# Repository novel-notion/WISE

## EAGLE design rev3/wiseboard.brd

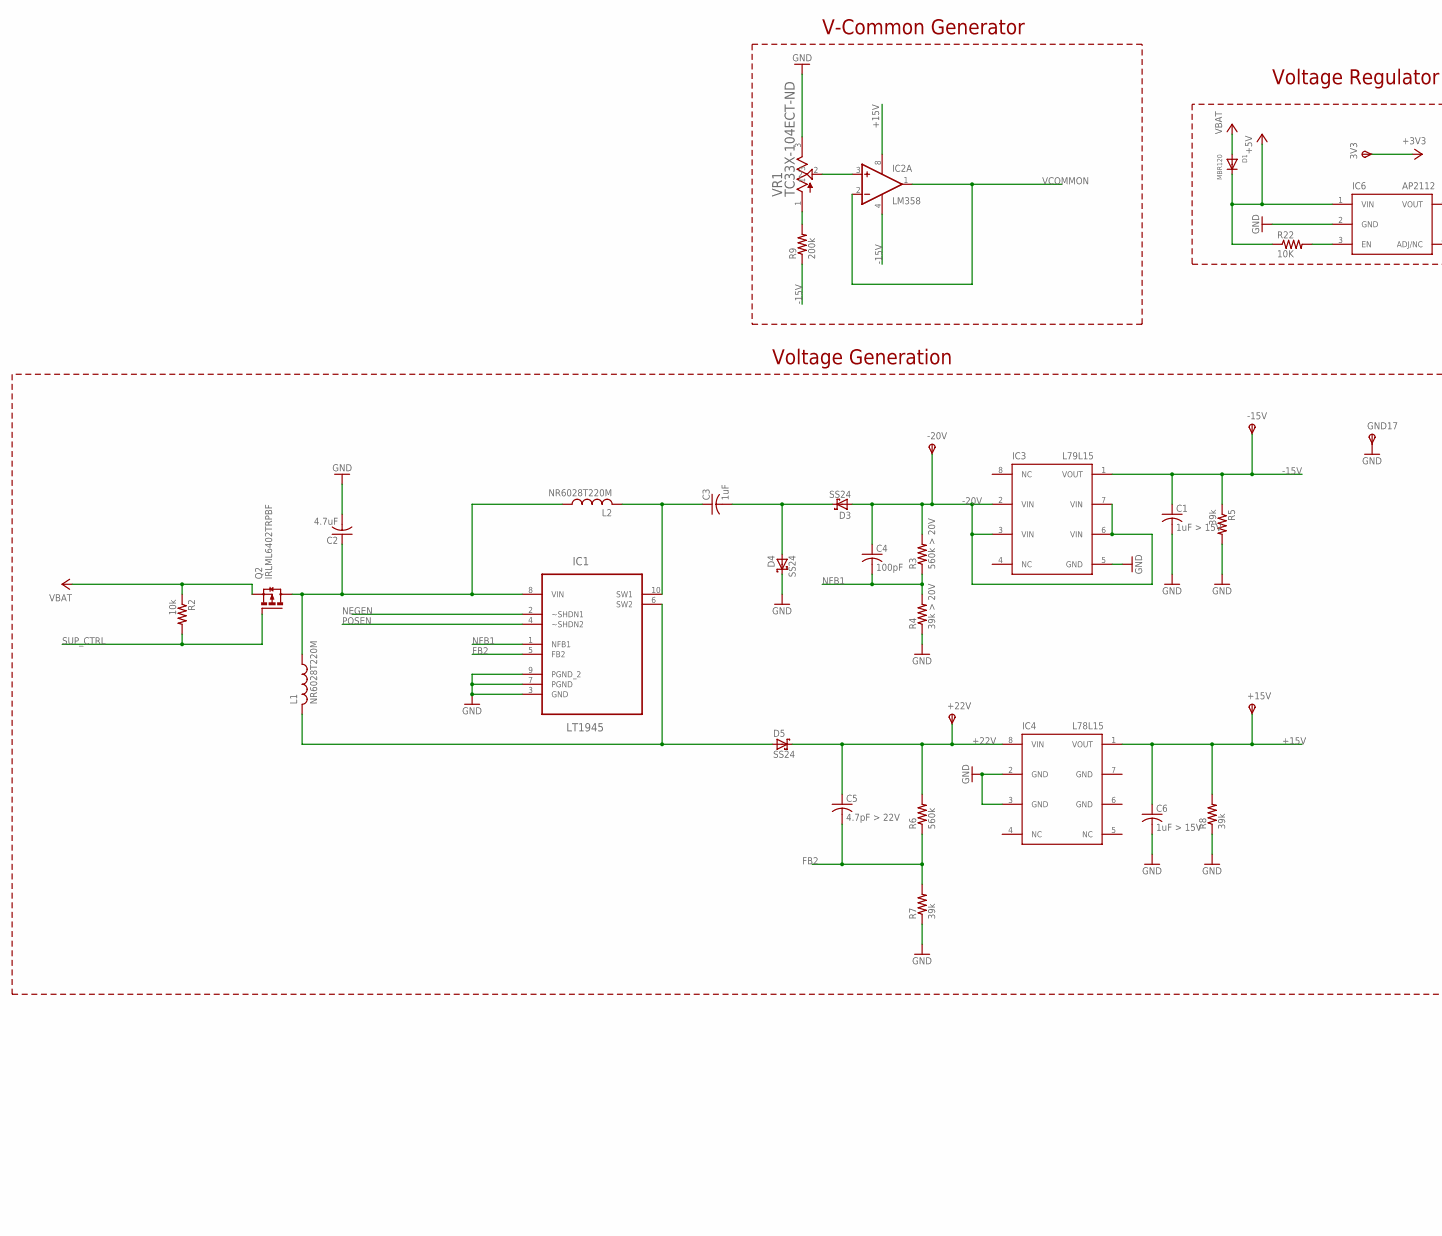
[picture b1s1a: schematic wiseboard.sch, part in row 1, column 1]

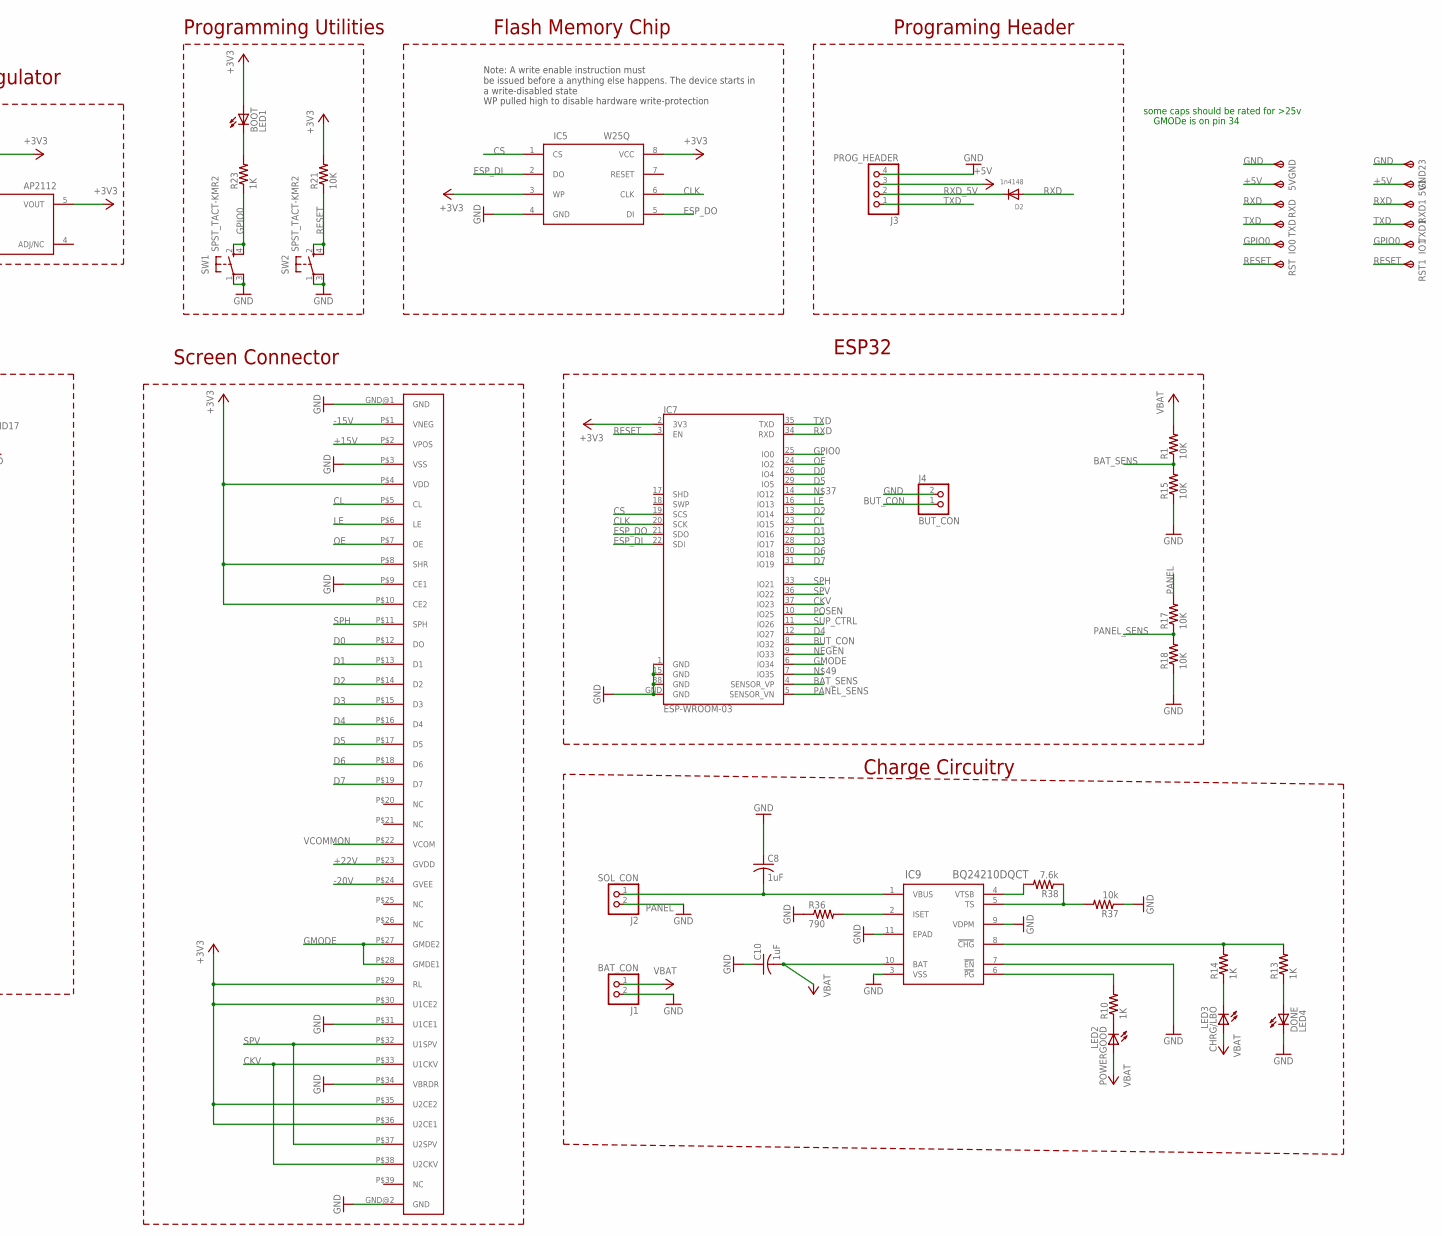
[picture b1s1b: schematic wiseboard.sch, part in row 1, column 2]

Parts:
3V3, 5V, 5V1: TPSTP20R; TP20R
+15V, +22V: TPSTP20R; TP20R
-15V, -20V: TPSTP20R; TP20R
BOOT: LED1; CHIP-LED0805
C1, C6: 1uF > 15V; C0805
C2: 4.7uF; C0805
C3, C8, C10: 1uF; C0805
C4: 100pF; C0805
C5: 4.7pF > 22V; C0805
CHRG/LBO: LED3; CHIP-LED0805
D1: MBR120; SOD-123
D2: 1n4148; SOD-123
D3, D4, D5: SS24; DO214AA
DONE: LED4; CHIP-LED0805
GND, GND17, GND23: TPSTP20SQ; TP20SQ
IC1: LT1945; SOP50P490X110-10N
IC2: LM358; SO08
IC3: L79L15; SO8
IC4: L78L15; SO8
IC5: W25Q; SO8
IC6: AP2112; SOT95P280X145-5N
IC7: ESP-WROOM-03
IC9: BQ24210DQCT; DQC10_P84X2P4
IO0, IO1: TPSTP20R; TP20R
J1: BAT_CON; EDGE_CON_2
J2: SOL_CON; EDGE_CON_2
J3: PROG_HEADER; EDGE_CON_4
J4: BUT_CON; EDGE_CON_2
L1, L2: NR6028T220M
POWERGOOD: LED2; CHIP-LED0805
Q2: IRLML6402TRPBF; SOT23
R1, R15, R17, R18, R21, R22: 10K; R0805
R2, R37: 10k; R0805
R3: 560k > 20V; R0805
R4: 39k > 20V; R0805
R5, R7, R8: 39k; R0805
R6: 560k; R0805
R9: 200k; R0805
R10, R13, R14, R23: 1K; R0805
R36: 790; R0805
R38: 7.6k; R0805
RST, RST1: TPSTP20R; TP20R
RXD, RXD1: TPSTP20R; TP20R
SW1, SW2: SPST_TACT-KMR2; KMR2
TXD, TXD1: TPSTP20R; TP20R
U$4: FH26W-39S; HFQ339CT-ND
VR1: TC33X-104ECT-ND; TRIM_TC33X-2-103E

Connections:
+3V3: 3V3.TP, BOOT.A, IC5.3 (WP), IC5.8 (VCC), IC6.5 (VOUT), IC7.2 (3V3), R21.2, U$4.P$4 (VDD), U$4.P$8 (SHR), U$4.P$10 (CE2), U$4.P$29 (RL), U$4.P$30 (U1CE2), U$4.P$35 (U2CE2), U$4.P$36 (U2CE1)
+5V: 5V.TP, 5V1.TP, D1.C, IC6.1 (VIN), J3.3, R22.1
+15V: +15V.TP, C6.1, IC2.8 (V+), IC4.1 (VOUT), R8.2, U$4.P$2 (VPOS)
+22V: +22V.TP, C5.1, D5.C, IC4.8 (VIN), R6.2, U$4.P$23 (GVDD)
-15V: -15V.TP, C1.1, IC2.4 (V-), IC3.1 (VOUT), R5.1, R9.1, U$4.P$1 (VNEG)
-20V: -20V.TP, C4.1, D3.A, IC3.2 (VIN), IC3.3 (VIN), IC3.6 (VIN), IC3.7 (VIN), R3.2, U$4.P$24 (GVEE)
BAT_SENS: IC7.4 (SENSOR_VP), R1.1, R15.2
BUT_CON: IC7.8 (IO32), J4.1 (2)
CKV: IC7.37 (IO23), U$4.P$33 (U1CKV), U$4.P$38 (U2CKV)
CL: IC7.23 (IO15), U$4.P$5 (CL)
CLK: IC5.6 (CLK), IC7.20 (SCK)
CS: IC5.1 (CS), IC7.19 (SCS)
D0: IC7.26 (IO4), U$4.P$12 (DO)
D1: IC7.27 (IO16), U$4.P$13 (D1)
D2: IC7.13 (IO14), U$4.P$14 (D2)
D3: IC7.28 (IO17), U$4.P$15 (D3)
D4: IC7.12 (IO27), U$4.P$16 (D4)
D5: IC7.29 (IO5), U$4.P$17 (D5)
D6: IC7.30 (IO18), U$4.P$18 (D6)
D7: IC7.31 (IO19), U$4.P$19 (D7)
ESP_DI: IC5.2 (DO), IC7.22 (SDI)
ESP_DO: IC5.5 (DI), IC7.21 (SDO)
FB2: C5.2, IC1.5 (FB2), R6.1, R7.2
GMODE: IC7.6 (IO34), U$4.P$27 (GMDE2), U$4.P$28 (GMDE1)
GND: C1.2, C2.2, C6.2, C8.1, C10.1, D4.C, DONE.C, GND.TP, GND17.TP, GND23.TP, IC1.3 (GND), IC1.7 (PGND), IC1.9 (PGND_2), IC3.5 (GND), IC4.2 (GND), IC4.3 (GND), IC5.4 (GND), IC6.2 (GND), IC7.1 (GND), IC7.15 (GND), IC7.38 (GND), IC7.GND, IC9.3 (VSS), IC9.7 (!EN), IC9.9 (VDPM), IC9.11 (EPAD), J1.2 (1), J2.2 (1), J3.4, J4.2 (1), R4.1, R5.2, R7.1, R8.1, R15.1, R18.1, R36.1, R37.1, SW1.1, SW1.3 (P1), SW2.1, SW2.3 (P1), U$4.GND@1 (GND), U$4.GND@2 (GND), U$4.P$3 (VSS), U$4.P$9 (CE1), U$4.P$31 (U1CE1), U$4.P$34 (VBRDR), VR1.3
GPIO0: IC7.25 (IO0), IO0.TP, IO1.TP, R23.1, SW1.2 (S), SW1.4 (S1)
LE: IC7.16 (IO13), U$4.P$6 (LE)
unnamed: IC2.3 (+IN), VR1.2
unnamed: C3.1, IC1.10 (SW1), L2.P$2 (2)
unnamed: C2.1, IC1.8 (VIN), L1.P$1 (1), L2.P$1 (1), Q2.3 (D)
unnamed: D5.A, IC1.6 (SW2), L1.P$2 (2)
unnamed: C3.2, D3.C, D4.A
unnamed: R9.2, VR1.1
unnamed: IC9.6 (!PG), R10.2
unnamed: CHRG/LBO.C, R14.1
unnamed: POWERGOOD.C, R10.1
unnamed: DONE.A, R13.1
unnamed: IC9.8 (!CHG), R13.2, R14.2
unnamed: IC9.2 (ISET), R36.2
unnamed: BOOT.C, R23.2
unnamed: IC6.3 (EN), R22.2
unnamed: IC9.5 (TS), R37.2, R38.1
unnamed: IC9.4 (VTSB), R38.2
NEGEN: IC1.2 (~SHDN1), IC7.9 (IO33)
NFB1: C4.2, IC1.1 (NFB1), R3.1, R4.2
OE: IC7.24 (IO2), U$4.P$7 (OE)
PANEL: C8.2, IC9.1 (VBUS), J2.1 (2), R17.2
PANEL_SENS: IC7.5 (SENSOR_VN), R17.1, R18.2
POSEN: IC1.4 (~SHDN2), IC7.10 (IO25)
RESET: IC7.3 (EN), R21.1, RST.TP, RST1.TP, SW2.2 (S), SW2.4 (S1)
RXD: D2.A, IC7.34 (RXD), RXD.TP, RXD1.TP
RXD_5V: D2.C, J3.2
SPH: IC7.33 (IO21), U$4.P$11 (SPH)
SPV: IC7.36 (IO22), U$4.P$32 (U1SPV), U$4.P$37 (U2SPV)
SUP_CTRL: IC7.11 (IO26), Q2.1 (G), R2.2
TXD: IC7.35 (TXD), J3.1, TXD.TP, TXD1.TP
VBAT: C10.2, CHRG/LBO.A, D1.A, IC9.10 (BAT), J1.1 (2), POWERGOOD.A, Q2.2 (S), R1.2, R2.1
VCOMMON: IC2.1 (OUT), IC2.2 (-IN), U$4.P$22 (VCOM)

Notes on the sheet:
V-Common Generator
Programming Utilities
Programing Header
Voltage Generation
Charge Circuitry
ESP32
Voltage Regulator
Screen Connector
Note: A write enable instruction must be issued before a anything else happens. The device starts in a write-disabled state
WP pulled high to disable hardware write-protection
Flash Memory Chip
some caps should be rated for >25v
GMODe is on pin 34

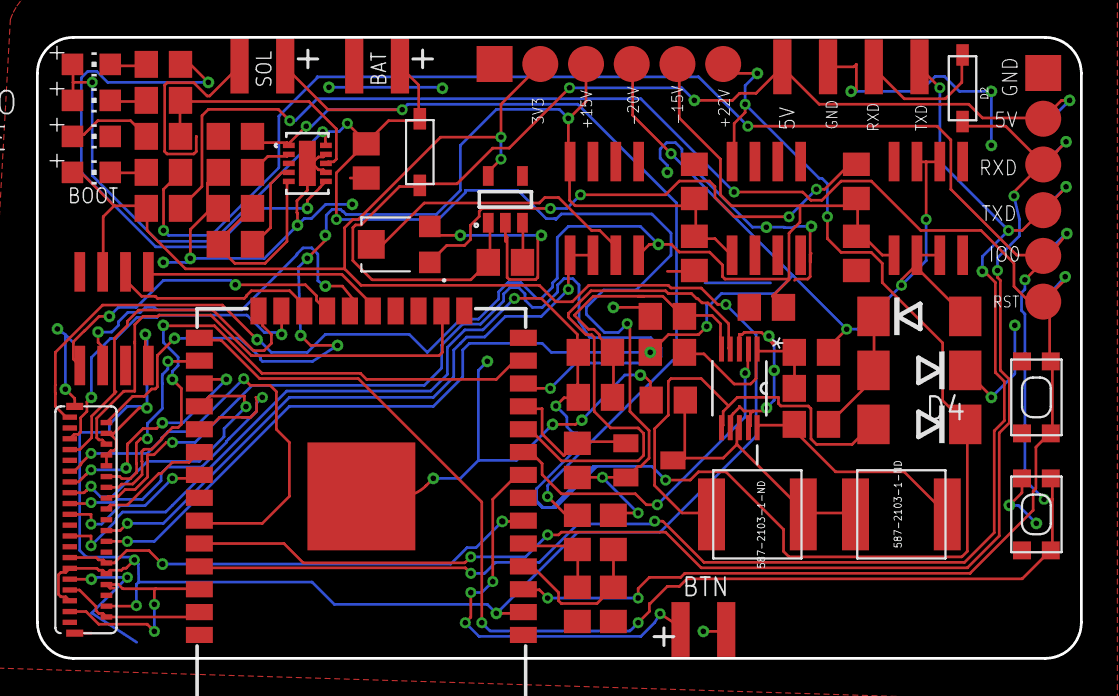
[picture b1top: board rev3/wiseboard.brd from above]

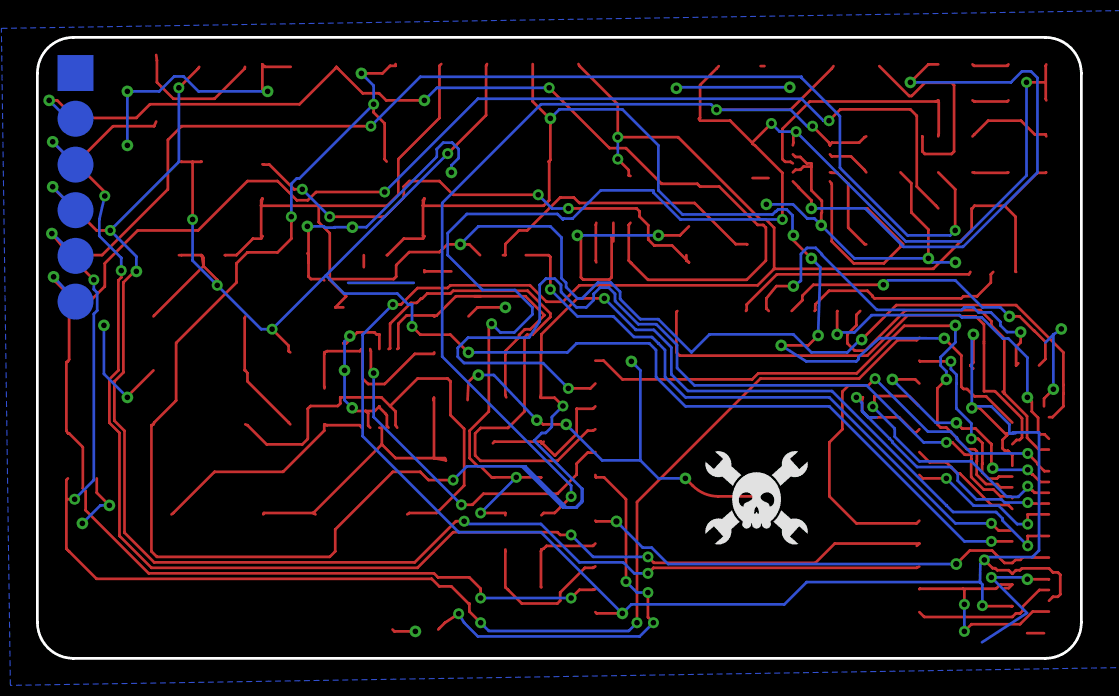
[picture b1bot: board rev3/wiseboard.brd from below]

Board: 2 copper layers, 58.0 x 34.5 mm, 75 parts (6 on the bottom side), 58 nets.

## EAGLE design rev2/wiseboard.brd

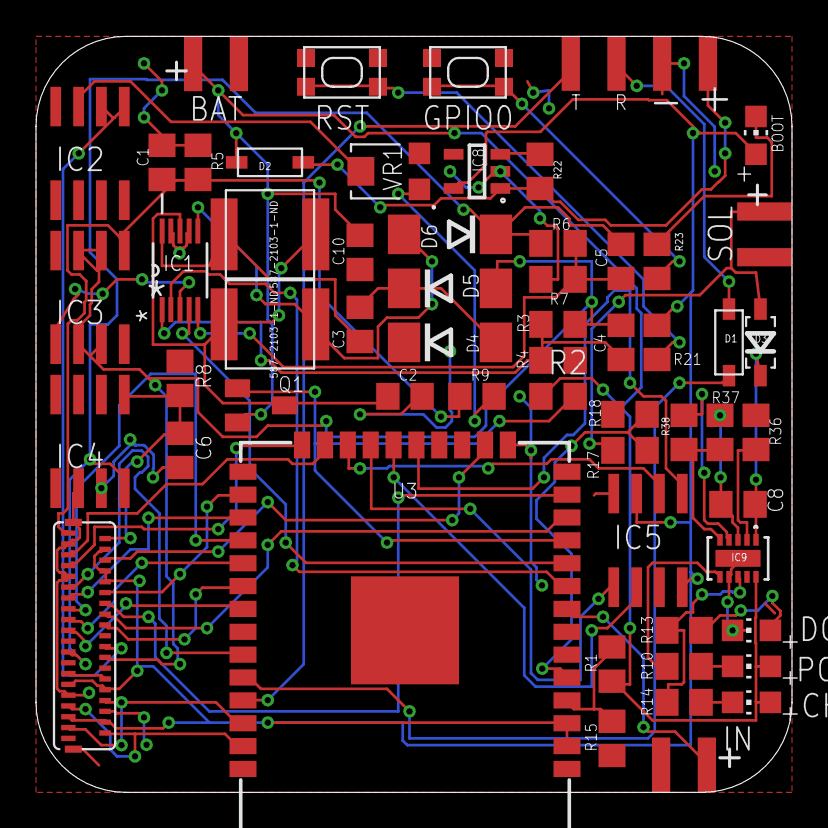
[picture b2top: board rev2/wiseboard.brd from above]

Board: 2 copper layers, 42.0 x 42.0 mm, 58 parts (0 on the bottom side), 59 nets.

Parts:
22: 587-2103-1-ND
BOOT: LED1; CHIP-LED0805
C1, C2, C3, C6: 1uF; C0805
C4, C5, C8, C10: 10uF; C0805
CHRG/LBO: LED3; CHIP-LED0805
D1: MBR120VLSFT1G; SOD-123
D2: MBR120; SOD-123
D3: 1n4148; SOD-123
D4, D5, D6: SS24; DO214AA
DONE: LED4; CHIP-LED0805
IC1: LT1945; SOP50P490X110-10N
IC2: LM358; SO08
IC3: L79L15; SO8
IC4: L78L15; SO8
IC5: W25Q; SO8
IC8: IC6; SOT95P280X145-5N
IC9: BQ24210DQCT; DQC10_P84X2P4
J1: BAT_CON; EDGE_CON_2
J2: SOL_CON; EDGE_CON_2
J3: PROG_HEADER; EDGE_CON_4
J4: BUT_CON; EDGE_CON_2
POWERGOOD: LED2; CHIP-LED0805
Q1: IRLM; SOT23
R1, R15, R17, R18, R21, R22: 10K; R0805
R2, R37: 10k; R0805
R3: 470k; R0805
R4, R5, R7, R8: 39k; R0805
R6: 560k; R0805
R9: 200k; R0805
R10, R13, R14, R23: 1K; R0805
R36: 790; R0805
R38: 7.6k; R0805
SW1, SW2: SPST_TACT-KMR2; KMR2
U3: ESP-WROOM-03
U$4: FH26W-39S; HFQ339CT-ND
U$5: 587-2103-1-ND
VR1: TC33X-104ECT-ND; TRIM_TC33X-2-103E

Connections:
+3V3: BOOT.A, IC5.3, IC5.8, IC8.5, R21.2, U3.2, U3.3, U$4.P$4, U$4.P$8, U$4.P$10, U$4.P$29, U$4.P$30, U$4.P$35, U$4.P$36
+5V: D2.C, IC8.1, J3.3, R22.1
+15V: C6.1, IC4.1, R8.2, U$4.P$2
+22V: C5.1, D6.C, IC4.8, R6.2, U$4.P$23
-15V: C1.1, IC3.1, R5.1, R9.1, U$4.P$1
-20V: C4.1, D5.A, IC3.2, IC3.3, IC3.6, IC3.7, R3.2, U$4.P$24
BAT_SENS: R1.1, R15.2, U3.4
BUT_CON: J4.1, U3.8
CKV: U3.37, U$4.P$33, U$4.P$38
CL: U3.23, U$4.P$5
CLK: IC5.6, U3.20
D0: U3.26, U$4.P$12
D1: U3.27, U$4.P$13
D2: U3.13, U$4.P$14
D3: U3.28, U$4.P$15
D4: U3.12, U$4.P$16
D5: U3.29, U$4.P$17
D6: U3.30, U$4.P$18
D7: U3.31, U$4.P$19
ESP_DI: IC5.2, U3.22
ESP_DO: IC5.5, U3.21
FB2: C5.2, IC1.5, R6.1, R7.2
GMODE: U$4.P$27, U$4.P$28
GND: C1.2, C2.2, C6.2, C8.1, C10.1, D4.C, DONE.C, IC1.3, IC1.7, IC1.9, IC3.5, IC4.2, IC4.3, IC4.6, IC4.7, IC5.4, IC8.2, IC9.3, IC9.7, IC9.11, J1.2, J2.2, J3.4, J4.2, R4.1, R5.2, R7.1, R8.1, R15.1, R18.1, R36.1, R37.1, SW1.1, SW1.3, SW2.1, SW2.3, U3.1, U3.15, U3.38, U3.GND, U$4.GND@1, U$4.GND@2, U$4.P$3, U$4.P$9, U$4.P$31, U$4.P$34, VR1.3
GPIO0: R23.1, SW1.2, SW1.4
IC5: IC5.1, U3.19
LE: U3.16, U$4.P$6
unnamed: IC2.3, VR1.2
unnamed: 22.P$2, C3.1, IC1.10
unnamed: C8.2, D1.C, IC9.1
unnamed: 22.P$1, C2.1, IC1.8, Q1.3, U$5.P$2
unnamed: D6.A, IC1.6, U$5.P$1
unnamed: C3.2, D4.A, D5.C
unnamed: R9.2, VR1.1
unnamed: IC9.6, R10.2
unnamed: CHRG/LBO.C, R14.1
unnamed: POWERGOOD.C, R10.1
unnamed: DONE.A, R13.1
unnamed: IC9.8, R13.2, R14.2
unnamed: IC9.2, R36.2
unnamed: BOOT.C, R23.2
unnamed: IC8.3, R22.2
unnamed: IC9.5, R37.2, R38.1
unnamed: IC9.4, R38.2
NEGEN: IC1.2, U3.9
NFB1: C4.2, IC1.1, R3.1, R4.2
OE: U3.24, U$4.P$7
PANEL: D1.A, J2.1, R17.2
PANEL_SENS: R17.1, R18.2, U3.5
POSEN: IC1.4, U3.10
RESET: R21.1, SW2.2, SW2.4
RXD: D3.A, U3.34
RXD_5V: D3.C, J3.2
SPH: U3.33, U$4.P$11
SPV: U3.36, U$4.P$32, U$4.P$37
SUP_CTRL: Q1.1, R2.2, U3.11
TXD: J3.1, U3.35
VBAT: C10.2, CHRG/LBO.A, D2.A, IC9.10, J1.1, POWERGOOD.A, Q1.2, R1.2, R2.1
VCOMMON: IC2.1, IC2.2, U$4.P$22

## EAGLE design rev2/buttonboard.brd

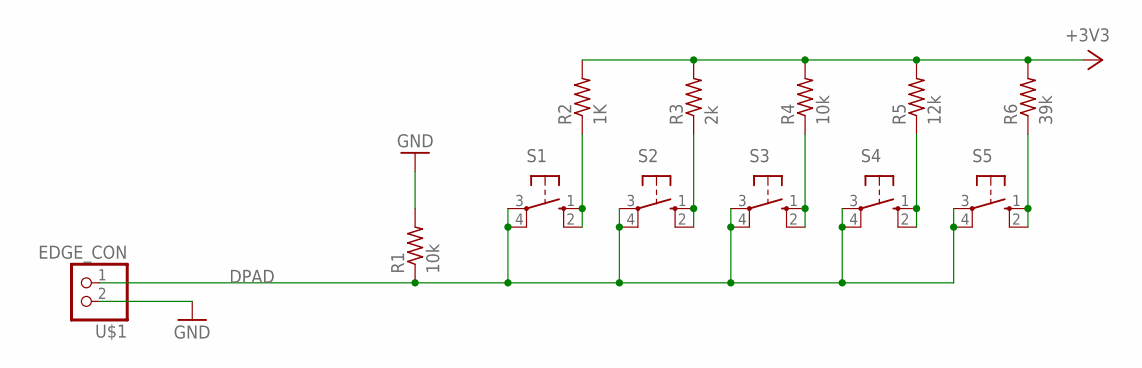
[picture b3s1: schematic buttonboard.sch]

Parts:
R1, R4: 10k; R0805
R2: 1K; R0805
R3: 2k; R0805
R5: 12k; R0805
R6: 39k; R0805
S1, S2, S3, S4, S5: 10-XX; B3F-10XX
U$1: EDGE_CON; EDGE_CON_2

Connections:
+3V3: R2.2, R3.2, R4.2, R5.2, R6.2
DPAD: R1.1, S1.3, S1.4 (P1), S2.3, S2.4 (P1), S3.3, S3.4 (P1), S4.3, S4.4 (P1), S5.3, S5.4 (P1), U$1.1 (2)
GND: R1.2
unnamed: R2.1, S1.1 (S), S1.2 (S1)
unnamed: R3.1, S2.1 (S), S2.2 (S1)
unnamed: R4.1, S3.1 (S), S3.2 (S1)
unnamed: R5.1, S4.1 (S), S4.2 (S1)
unnamed: R6.1, S5.1 (S), S5.2 (S1)

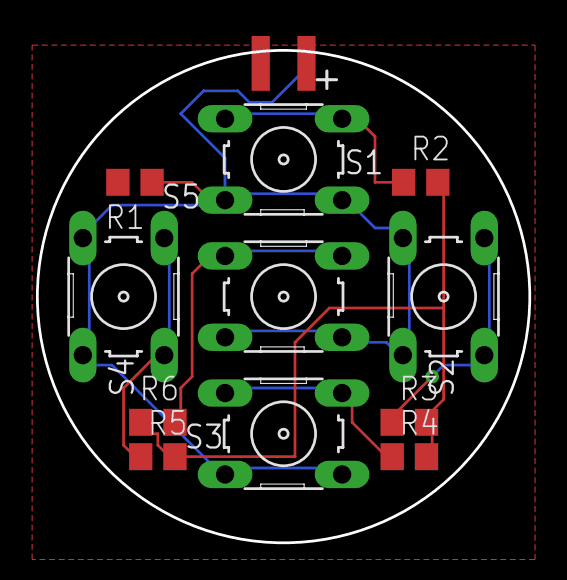
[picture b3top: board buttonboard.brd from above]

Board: 2 copper layers, 27.4 x 27.4 mm, 12 parts (0 on the bottom side), 7 nets.

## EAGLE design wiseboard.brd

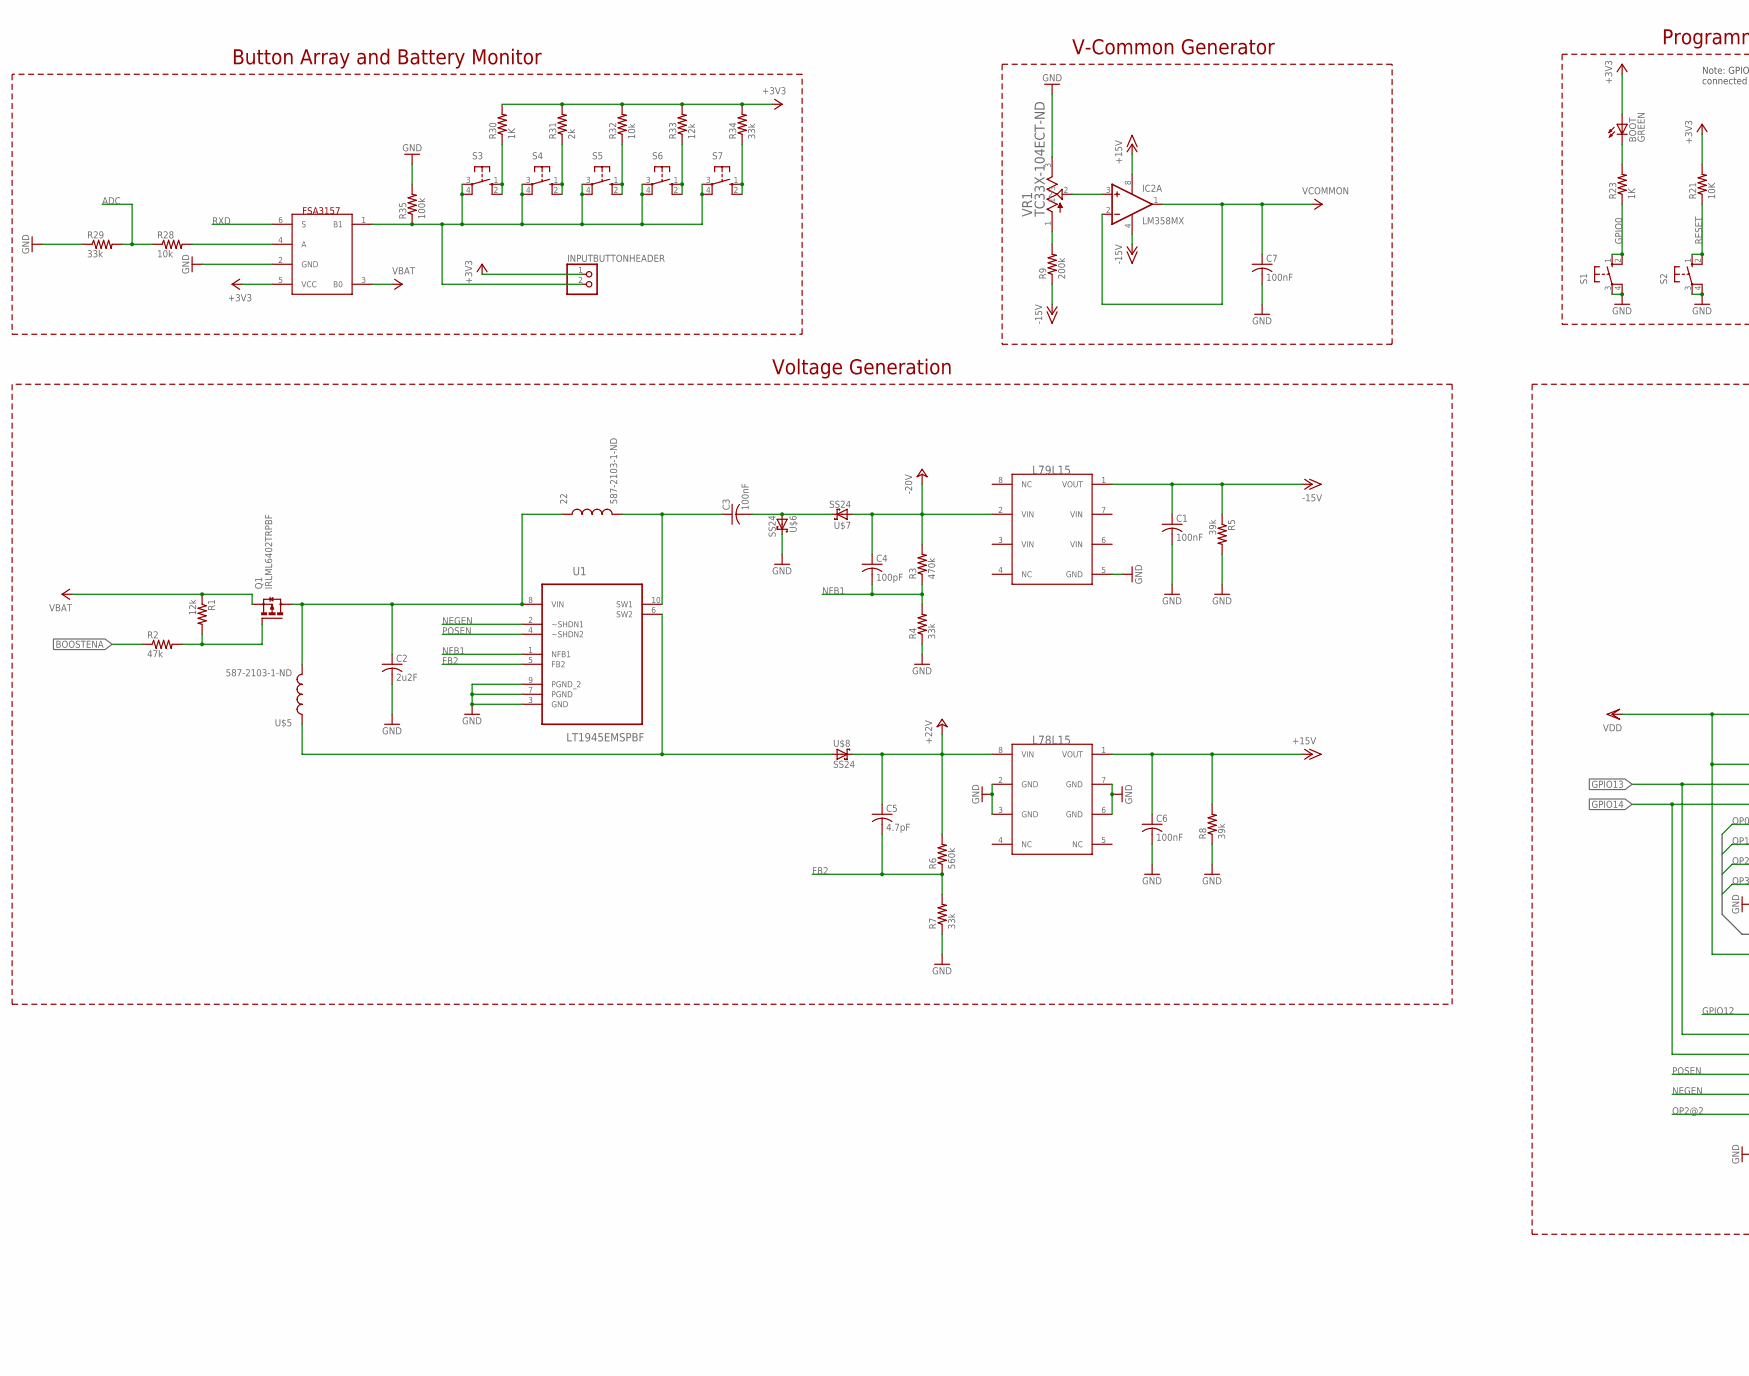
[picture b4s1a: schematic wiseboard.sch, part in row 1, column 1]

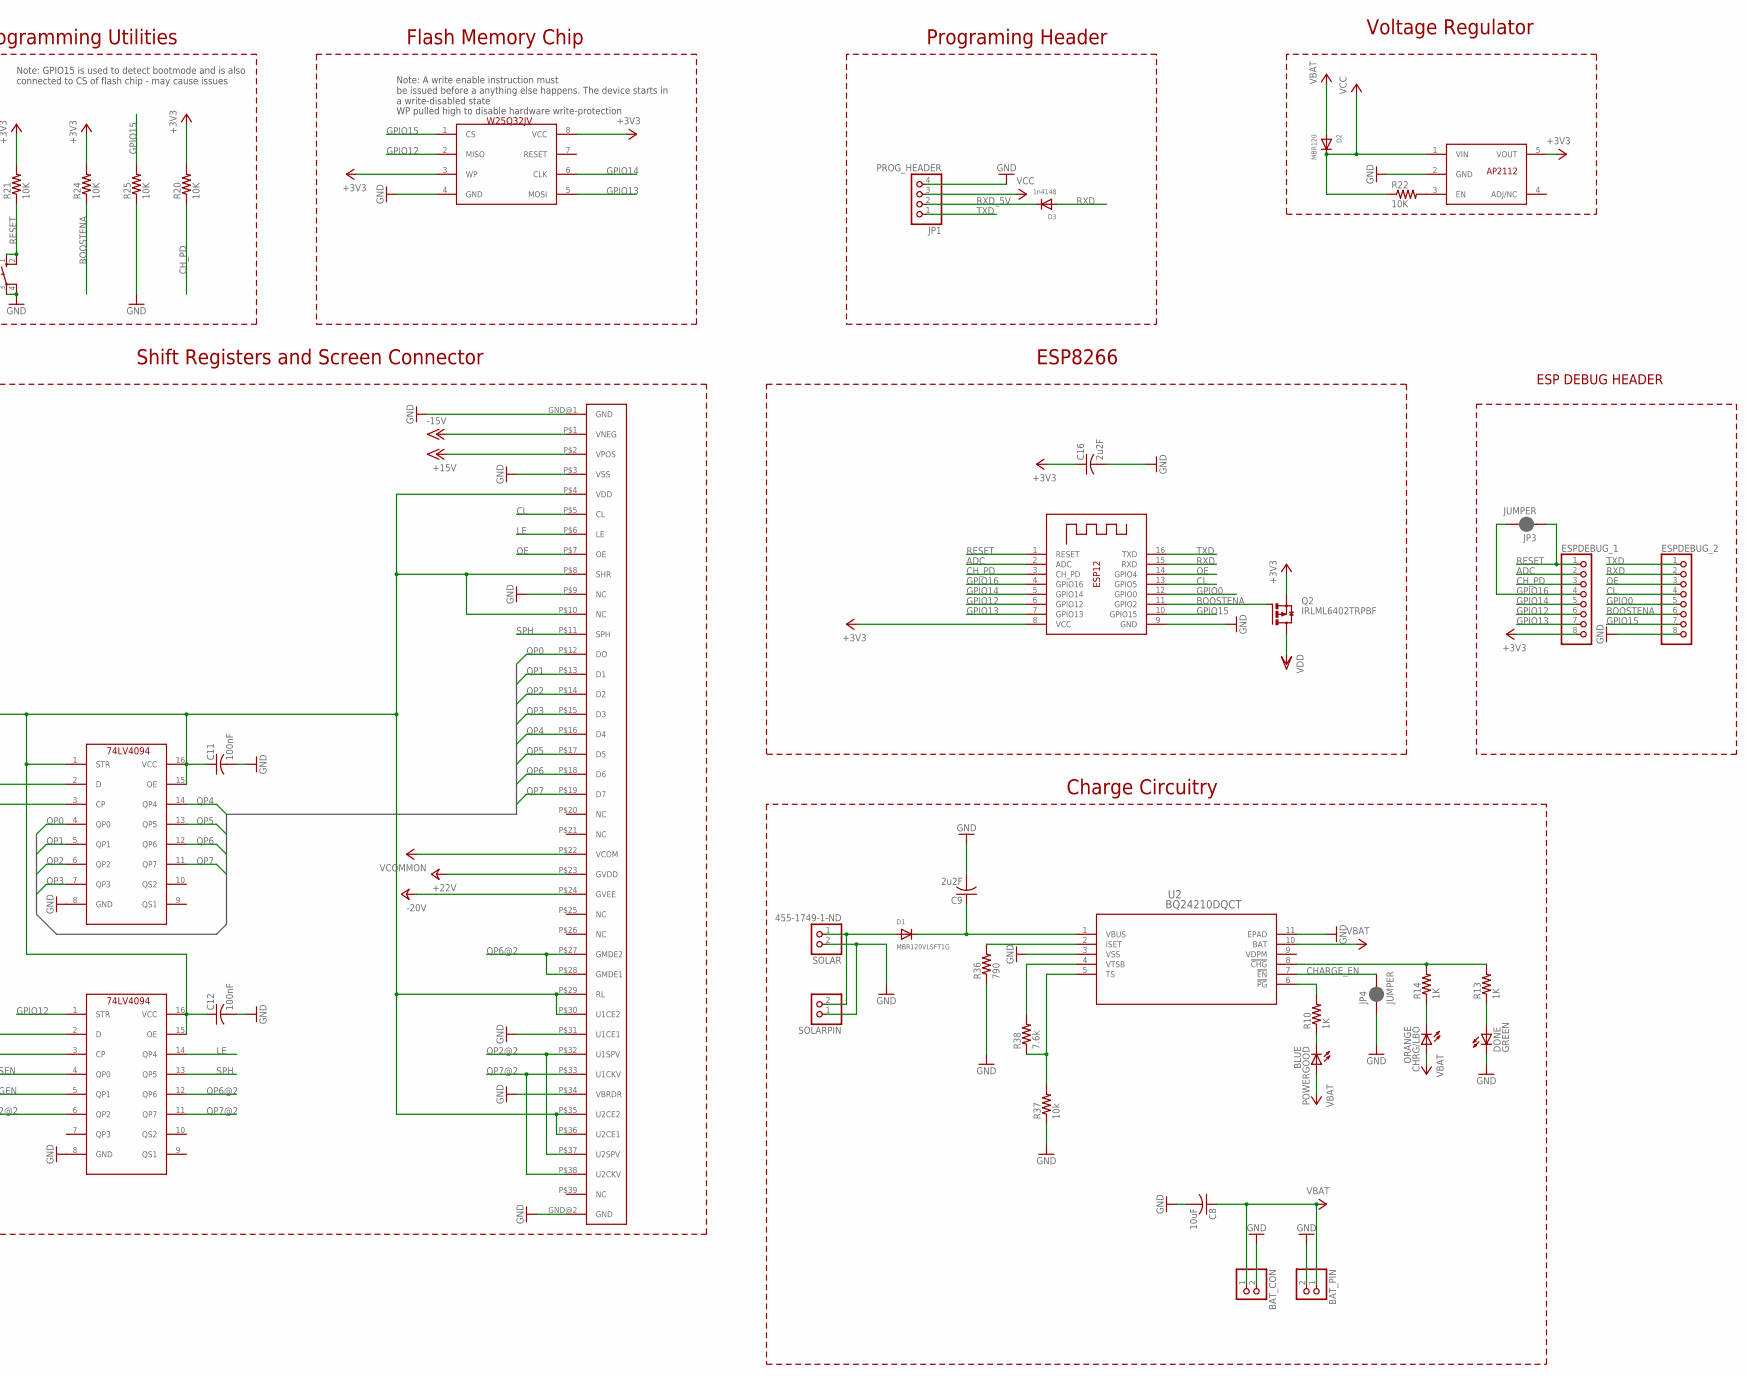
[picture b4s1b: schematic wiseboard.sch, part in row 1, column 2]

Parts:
22: 587-2103-1-ND
BAT_CON: JST_2PIN-SMT-RA; JST-PH-2-SMT-RA
BAT_PIN: PINHD-1X2; 1X02
BOOT: GREEN; CHIP-LED0805
C1, C3, C6, C7, C11, C12: 100nF; C1206
C2, C9, C16: 2u2F; C1206
C4: 100pF; C1206
C5: 4.7pF; C1206
C8: 10uF; C1206
CHRG/LBO: ORANGE; CHIP-LED0805
D1: MBR120VLSFT1G; SOD-123
D2: MBR120; SOD-123
D3: 1n4148; SOD-123
DONE: GREEN; CHIP-LED0805
ESPDEBUG_1, ESPDEBUG_2: PINHD-1X8; 1X08
IC2: LM358MX; SO08
INPUTBUTTONHEADER: PINHD-1X2; 1X02
JP1: PROG_HEADER; 1X04
JP3, JP4: JUMPER; SMT-JUMPER_2_NC_PASTE_NO-SILK
POWERGOOD: BLUE; CHIP-LED0805
Q1, Q2: IRLML6402TRPBF; SOT23
R1, R33: 12k; M1206
R2: 47k; M1206
R3: 470k; M1206
R4, R29, R34: 33k; M1206
R5, R8: 39k; R1206
R6: 560k; R1206
R7: 33k; R1206
R9: 200k; M1206
R10, R13, R14, R30: 1K; M1206
R20, R21, R22, R24, R25: 10K; R1206
R23: 1K; R1206
R28, R32: 10k; M1206
R31: 2k; M1206
R35: 100k; M1206
R36: 790; R1206
R37: 10k; R1206
R38: 7.6k; R1206
S1, S2, S3, S4, S5, S6, S7: 10-XX; B3F-10XX
SOLAR: 455-1749-1-ND; JST-PH-2-SMT-RA
SOLARPIN: PINHD-1X2; 1X02
U1: LT1945EMSPBF; SOP50P490X110-10N
U2: BQ24210DQCT; DQC10_P84X2P4
U$2: 497-7278-1-ND; SO8
U$3: 497-7303-1-ND; SO8
U$4: HFQ339CT-ND
U$5: 587-2103-1-ND
U$6, U$7, U$8: SS24; DO214AA
U$11, U$12: 1727-3473-ND; SO16
U$13: FSA3157; SC70-6L
U$14: AP2112K-3.3TRG1DICT-ND; SOT95P280X145-5N
U$23: W25Q32JVSSIQ; SO8
VR1: TC33X-104ECT-ND; TRIM_TC33X-2-103E
X1: 1528-1438-ND; ESP-12

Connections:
+3V3: BOOT.A, C16.1, ESPDEBUG_1.8, INPUTBUTTONHEADER.1, Q2.2 (S), R20.2, R21.2, R24.2, R30.2, R31.2, R32.2, R33.2, R34.2, U$13.5 (VCC), U$14.5 (VOUT), U$23.3 (WP), U$23.8 (VCC), X1.8 (VCC)
+15V: C6.1, IC2.8 (V+), R8.2, U$2.1 (VOUT), U$4.P$2 (VPOS)
+22V: C5.1, R6.2, U$2.8 (VIN), U$4.P$23 (GVDD), U$8.C
-15V: C1.1, IC2.4 (V-), R5.1, R9.1, U$3.1 (VOUT), U$4.P$1 (VNEG)
-20V: C4.1, R3.2, U$3.2 (VIN), U$4.P$24 (GVEE), U$7.A
ADC: ESPDEBUG_1.2, R28.1, R29.2, X1.2 (ADC)
BOOSTENA: ESPDEBUG_2.6, Q2.1 (G), R2.1, R24.1, X1.11 (GPIO2)
CHARGE_EN: JP4.2, U2.7 (!EN)
CH_PD: ESPDEBUG_1.3, R20.1, X1.3 (CH_PD)
CL: ESPDEBUG_2.4, U$4.P$5 (CL), X1.13 (GPIO5)
FB2: C5.2, R6.1, R7.2, U1.5 (FB2)
GND: BAT_CON.2 (1), BAT_PIN.2, C1.2, C2.2, C6.2, C7.2, C8.2, C9.2, C11.2, C12.2, C16.2, DONE.C, ESPDEBUG_2.8, JP1.4, JP4.1, R4.1, R5.2, R7.1, R8.1, R25.1, R29.1, R35.2, R36.1, R37.1, S1.3, S1.4 (P1), S2.3, S2.4 (P1), SOLAR.2 (1), SOLARPIN.1, U1.3 (GND), U1.7 (PGND), U1.9 (PGND_2), U2.3 (VSS), U2.11 (EPAD), U$2.2 (GND), U$2.3 (GND), U$2.6 (GND), U$2.7 (GND), U$3.5 (GND), U$4.GND@1 (GND), U$4.GND@2 (GND), U$4.P$3 (VSS), U$4.P$9 (NC), U$4.P$31 (U1CE1), U$4.P$34 (VBRDR), U$6.C, U$11.8 (GND), U$12.8 (GND), U$13.2 (GND), U$14.2 (GND), U$23.4 (GND), VR1.3, X1.9 (GND)
GPIO0: ESPDEBUG_2.5, R23.1, S1.1 (S), S1.2 (S1), X1.12 (GPIO0)
GPIO12: ESPDEBUG_1.6, U$12.1 (STR), U$23.2 (MISO), X1.6 (GPIO12)
GPIO13: ESPDEBUG_1.7, U$11.2 (D), U$12.2 (D), U$23.5 (MOSI), X1.7 (GPIO13)
GPIO14: ESPDEBUG_1.5, U$11.3 (CP), U$12.3 (CP), U$23.6 (CLK), X1.5 (GPIO14)
GPIO15: ESPDEBUG_2.7, R25.2, U$23.1 (CS), X1.10 (GPIO15)
GPIO16: ESPDEBUG_1.4, JP3.2, X1.4 (GPIO16)
LE: U$4.P$6 (LE), U$12.14 (QP4)
unnamed: IC2.3 (+IN), VR1.2
unnamed: 22.P$2 (2), C3.1, U1.10 (SW1)
unnamed: Q1.1 (G), R1.2, R2.2
unnamed: 22.P$1 (1), C2.1, Q1.3 (D), U1.8 (VIN), U$5.P$2 (2)
unnamed: U1.6 (SW2), U$5.P$1 (1), U$8.A
unnamed: C3.2, U$6.A, U$7.C
unnamed: D1.A, SOLAR.1 (2), SOLARPIN.2
unnamed: R9.2, VR1.1
unnamed: R10.2, U2.6 (!PG)
unnamed: CHRG/LBO.C, R14.1
unnamed: POWERGOOD.C, R10.1
unnamed: R28.2, U$13.4 (A)
unnamed: C9.1, D1.C, U2.1 (VBUS)
unnamed: DONE.A, R13.1
unnamed: R13.2, R14.2, U2.8 (!CHG)
unnamed: R36.2, U2.2 (ISET)
unnamed: BOOT.C, R23.2
unnamed: R22.2, U$14.3 (EN)
unnamed: INPUTBUTTONHEADER.2, R35.1, S3.3, S3.4 (P1), S4.3, S4.4 (P1), S5.3, S5.4 (P1), S6.3, S6.4 (P1), S7.3, S7.4 (P1), U$13.1 (B1)
unnamed: R30.1, S3.1 (S), S3.2 (S1)
unnamed: R37.2, R38.1, U2.5 (TS)
unnamed: R31.1, S4.1 (S), S4.2 (S1)
unnamed: R38.2, U2.4 (VTSB)
unnamed: R32.1, S5.1 (S), S5.2 (S1)
unnamed: R33.1, S6.1 (S), S6.2 (S1)
unnamed: R34.1, S7.1 (S), S7.2 (S1)
NEGEN: U1.2 (~SHDN1), U$12.5 (QP1)
NFB1: C4.2, R3.1, R4.2, U1.1 (NFB1)
OE: ESPDEBUG_2.3, U$4.P$7 (OE), X1.14 (GPIO4)
POSEN: U1.4 (~SHDN2), U$12.4 (QP0)
QP0: U$4.P$12 (DO), U$11.4 (QP0)
QP1: U$4.P$13 (D1), U$11.5 (QP1)
QP2: U$4.P$14 (D2), U$11.6 (QP2)
QP2@2: U$4.P$32 (U1SPV), U$4.P$37 (U2SPV), U$12.6 (QP2)
QP3: U$4.P$15 (D3), U$11.7 (QP3)
QP4: U$4.P$16 (D4), U$11.14 (QP4)
QP5: U$4.P$17 (D5), U$11.13 (QP5)
QP6: U$4.P$18 (D6), U$11.12 (QP6)
QP6@2: U$4.P$27 (GMDE2), U$4.P$28 (GMDE1), U$12.12 (QP6)
QP7: U$4.P$19 (D7), U$11.11 (QP7)
QP7@2: U$4.P$33 (U1CKV), U$4.P$38 (U2CKV), U$12.11 (QP7)
RESET: ESPDEBUG_1.1, JP3.1, R21.1, S2.1 (S), S2.2 (S1), X1.1 (RESET)
RXD: D3.A, ESPDEBUG_2.2, U$13.6 (S), X1.15 (RXD)
RXD_5V: D3.C, JP1.2
SPH: U$4.P$11 (SPH), U$12.13 (QP5)
TXD: ESPDEBUG_2.1, JP1.1, X1.16 (TXD)
VBAT: BAT_CON.1 (2), BAT_PIN.1, C8.1, CHRG/LBO.A, D2.A, POWERGOOD.A, Q1.2 (S), R1.1, U2.10 (BAT), U$13.3 (B0)
VCC: D2.C, JP1.3, R22.1, U$14.1 (VIN)
VCOMMON: C7.1, IC2.1 (OUT), IC2.2 (-IN), U$4.P$22 (VCOM)
VDD: C11.1, C12.1, Q2.3 (D), U$4.P$4 (VDD), U$4.P$8 (SHR), U$4.P$10 (NC), U$4.P$29 (RL), U$4.P$30 (U1CE2), U$4.P$35 (U2CE2), U$4.P$36 (U2CE1), U$11.1 (STR), U$11.15 (OE), U$11.16 (VCC), U$12.15 (OE), U$12.16 (VCC)

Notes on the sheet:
Button Array and Battery Monitor
V-Common Generator
Programming Utilities
Programing Header
Voltage Generation
Charge Circuitry
ESP8266
Voltage Regulator
Shift Registers and Screen Connector
ESP DEBUG HEADER
Note: GPIO15 is used to detect bootmode and is also connected to CS of flash chip - may cause issues
Note: A write enable instruction must be issued before a anything else happens. The device starts in a write-disabled state
WP pulled high to disable hardware write-protection
Flash Memory Chip

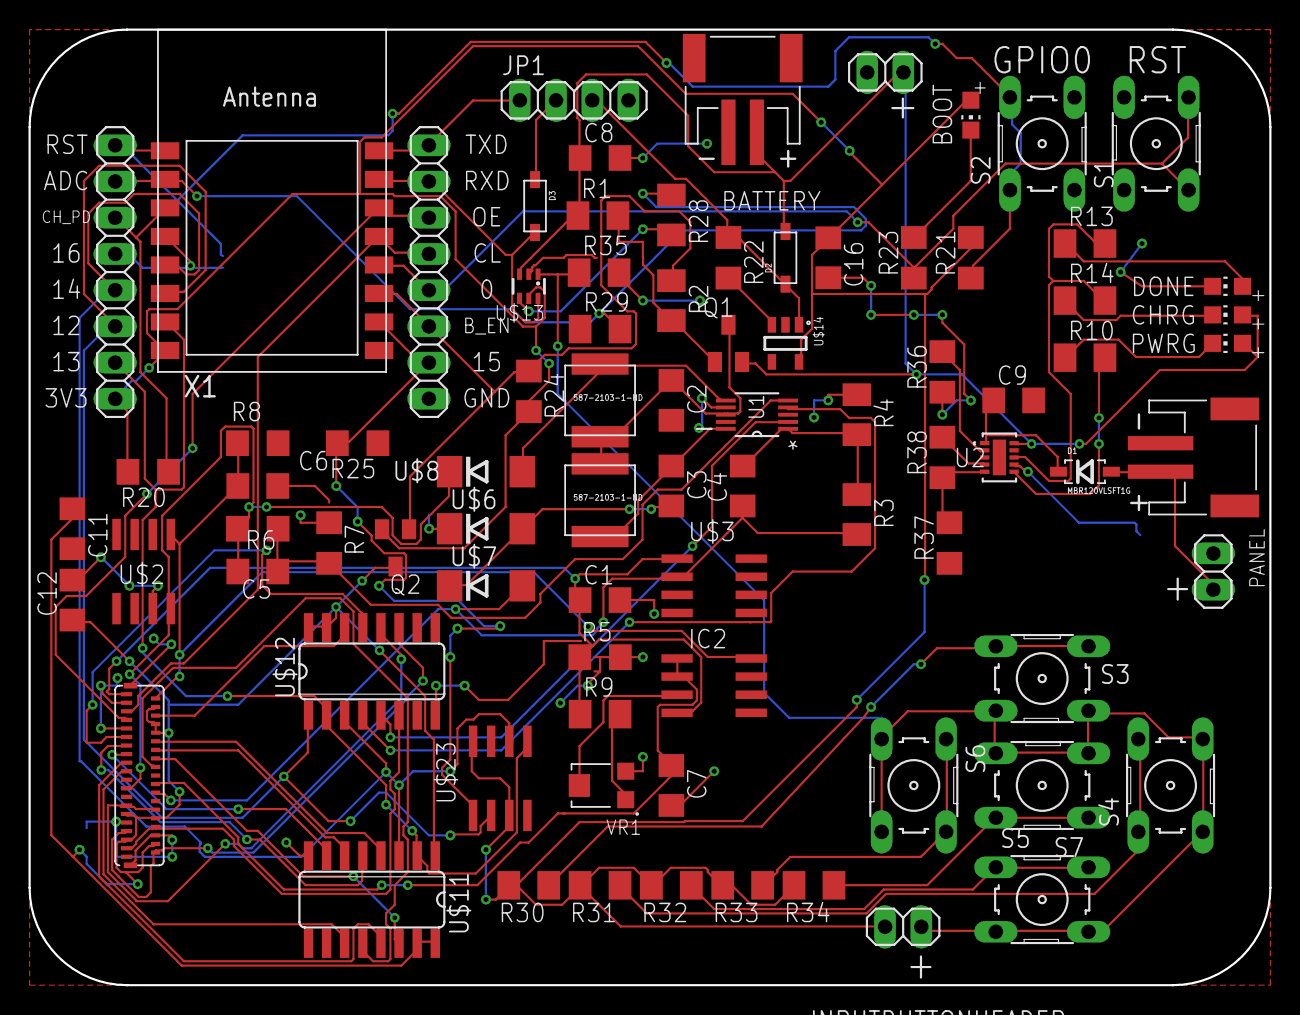
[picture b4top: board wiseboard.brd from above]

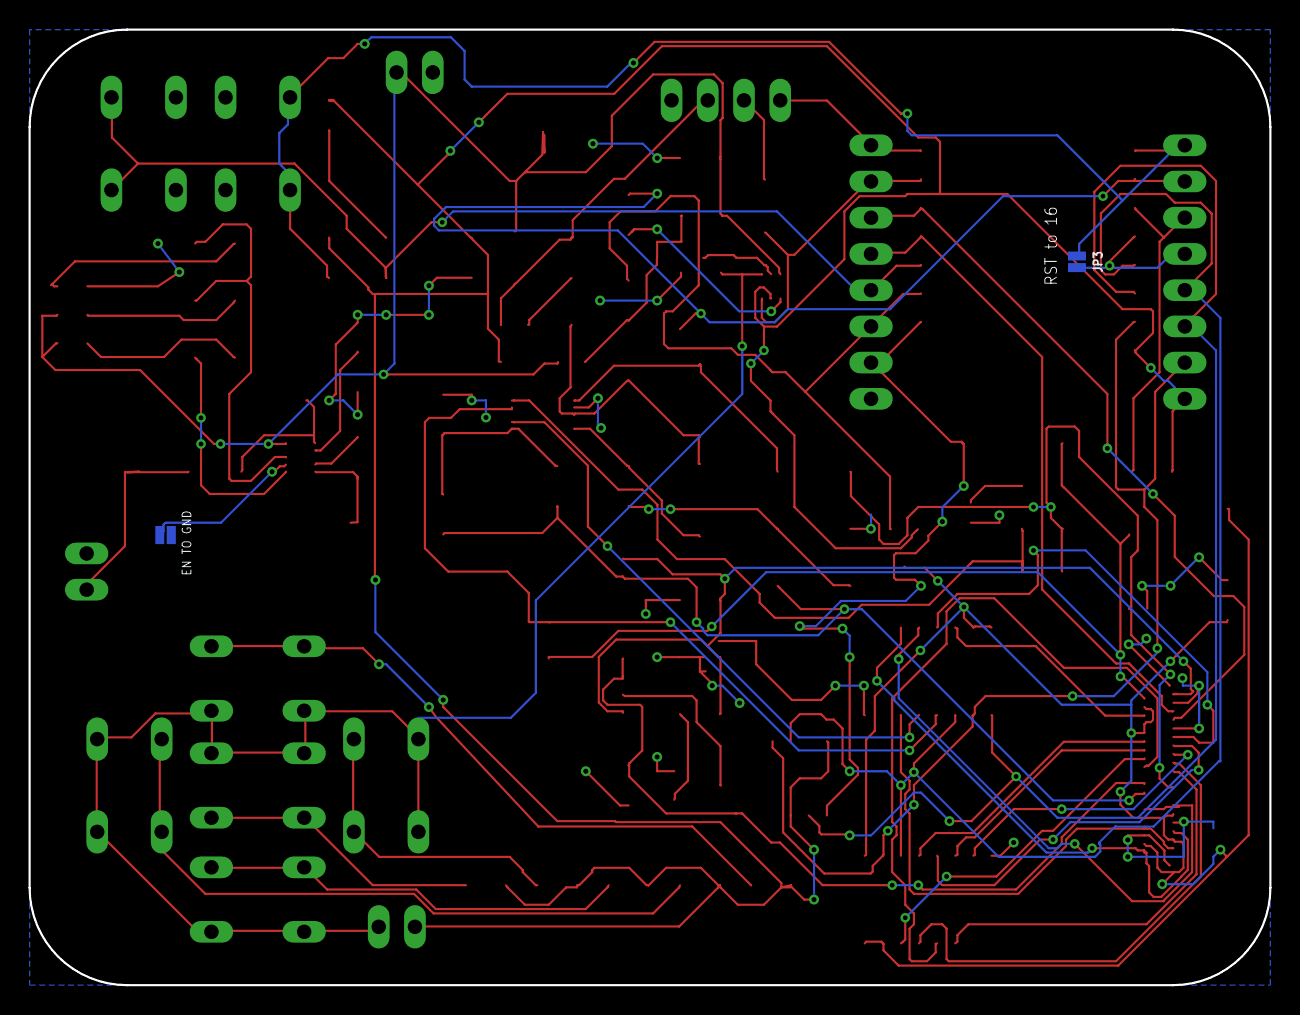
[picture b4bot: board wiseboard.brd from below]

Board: 2 copper layers, 87.0 x 67.0 mm, 85 parts (2 on the bottom side), 69 nets.

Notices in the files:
parts and their libraries:
Sparkfun-Passives: Licensing: Creative Commons ShareAlike 4.0 International - https://creativecommons.org/licenses/by-sa/4.0
